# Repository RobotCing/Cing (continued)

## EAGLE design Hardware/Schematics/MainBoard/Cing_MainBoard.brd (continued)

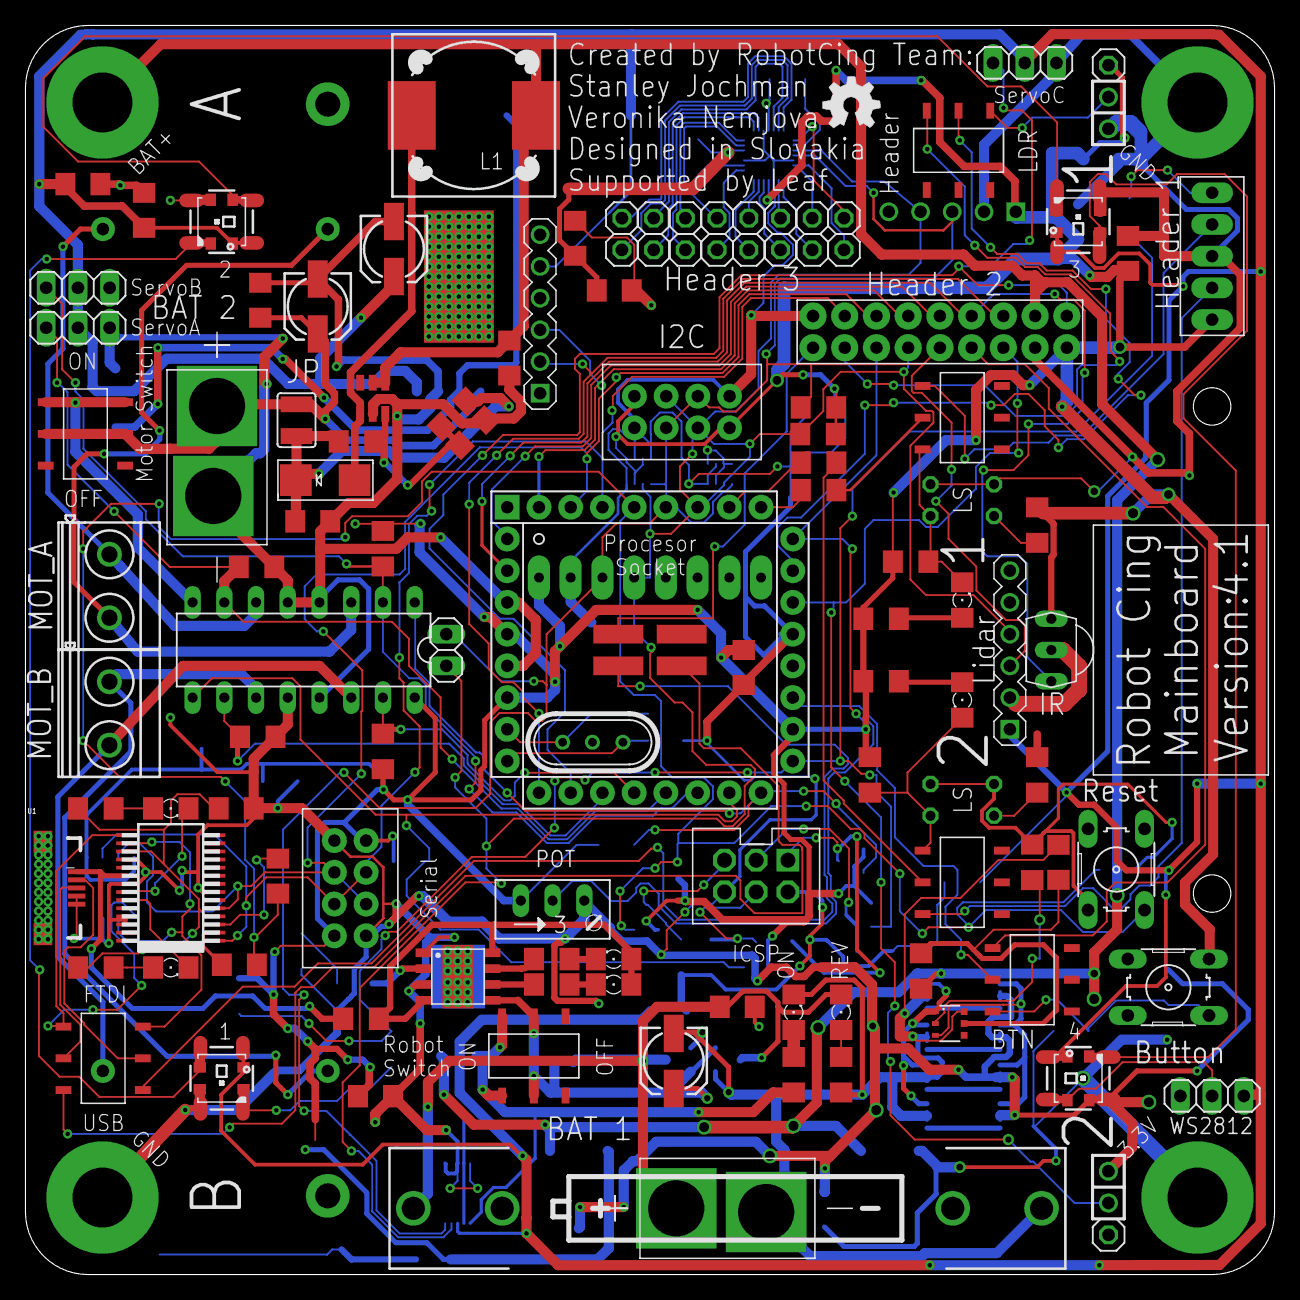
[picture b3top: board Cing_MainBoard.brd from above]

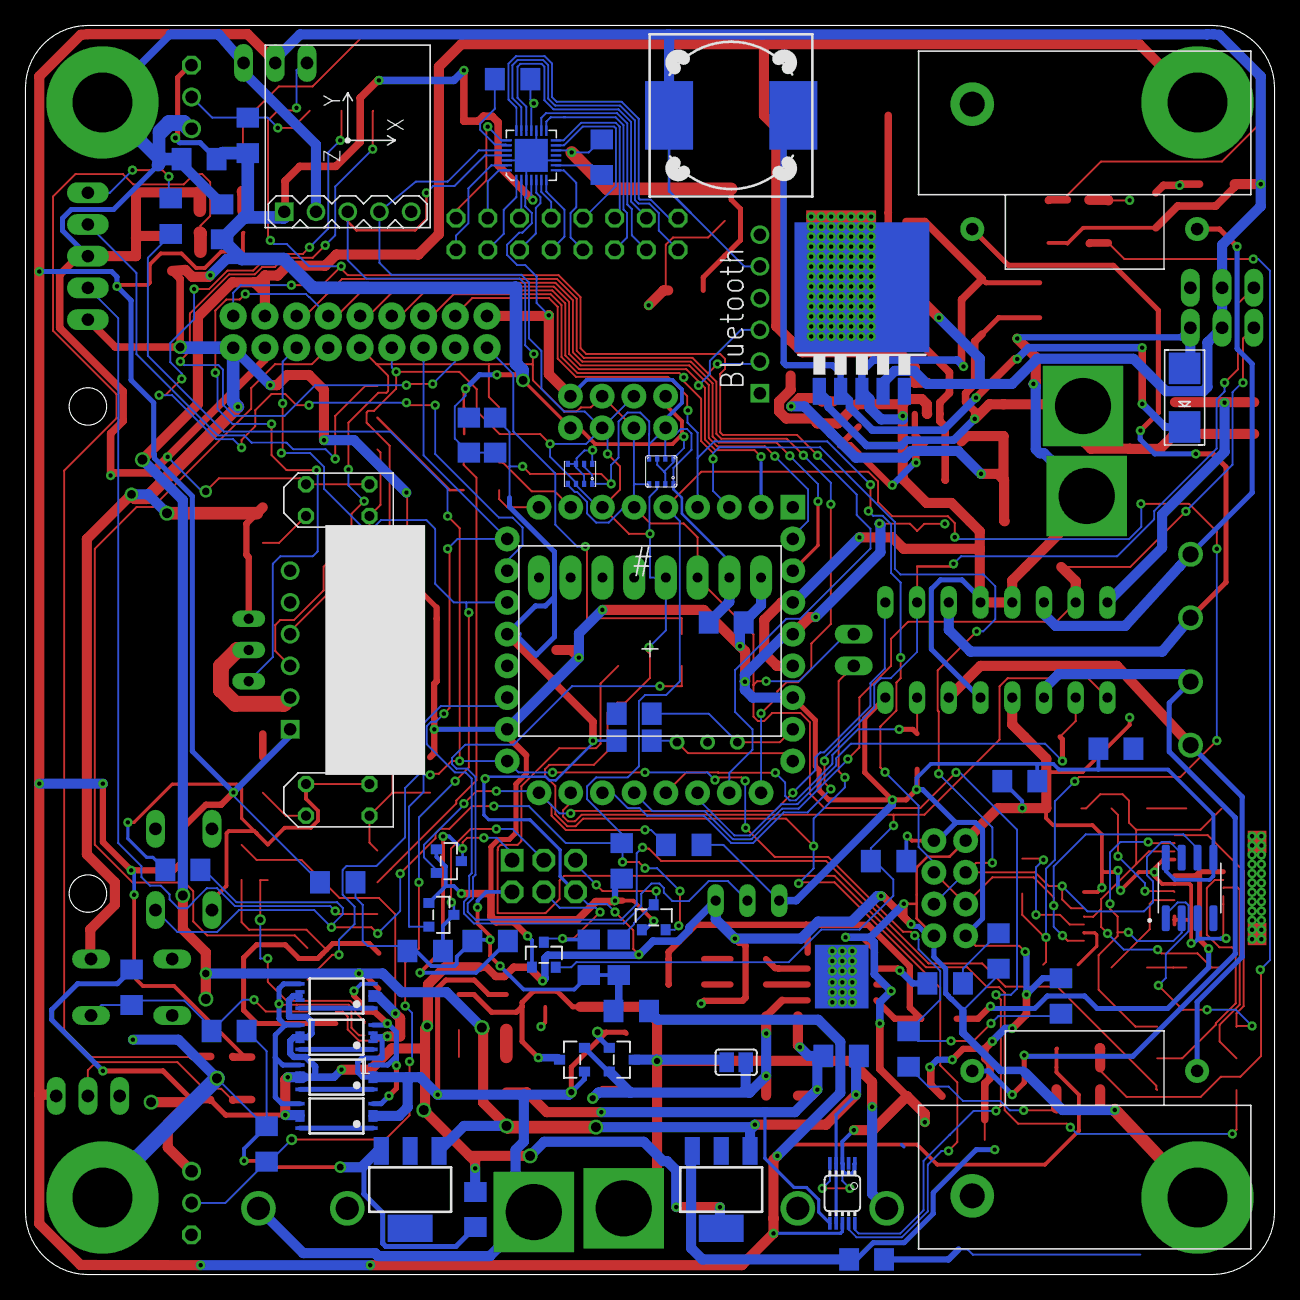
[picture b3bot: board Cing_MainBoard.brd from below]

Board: 2 copper layers, 100.0 x 100.0 mm, 186 parts (58 on the bottom side), 118 nets.

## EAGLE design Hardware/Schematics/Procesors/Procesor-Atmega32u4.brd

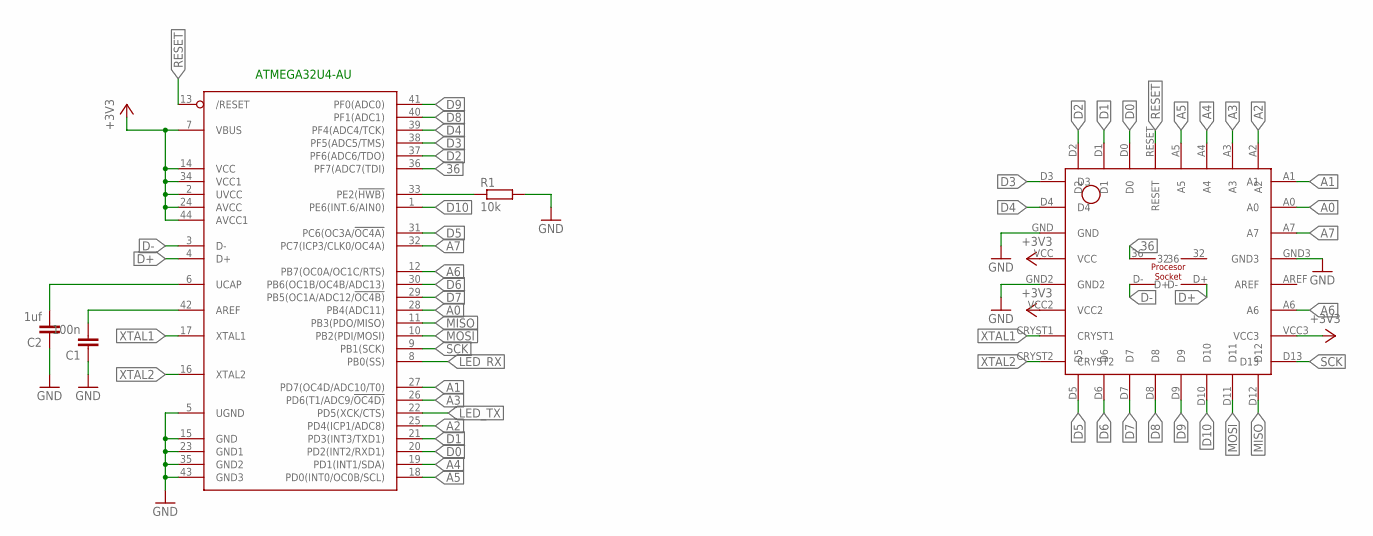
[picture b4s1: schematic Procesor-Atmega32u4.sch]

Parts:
ATMEGA32U4-AU: ATMEGA32U4-AU; TQFP44
C1: 100n; C1206
C2: 1uf; C1206K
R1: 10k; R1206
U$2: PROCESSOR-SOCKET; PROCESOR

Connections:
36: ATMEGA32U4-AU.36 (PF7(ADC7(TDI)), U$2.36
+3V3: ATMEGA32U4-AU.2 (UVCC), ATMEGA32U4-AU.7 (VBUS), ATMEGA32U4-AU.14 (VCC), ATMEGA32U4-AU.24 (AVCC), ATMEGA32U4-AU.34 (VCC1), ATMEGA32U4-AU.44 (AVCC1), U$2.VCC, U$2.VCC2, U$2.VCC3
A0: ATMEGA32U4-AU.28 (PB4(ADC11)), U$2.A0
A1: ATMEGA32U4-AU.27 (PD7(OC4D/ADC10/T0)), U$2.A1
A2: ATMEGA32U4-AU.25 (PD4(ICP1/ADC8)), U$2.A2
A3: ATMEGA32U4-AU.26 (PD6(T1/ADC9/!OC4D)), U$2.A3
A4: ATMEGA32U4-AU.19 (PD1(INT1/SDA)), U$2.A4
A5: ATMEGA32U4-AU.18 (PD0(INT0/OC0B/SCL)), U$2.A5
A6: ATMEGA32U4-AU.12 (PB7(OC0A/OC1C/RTS)), U$2.A6
A7: ATMEGA32U4-AU.32 (PC7(ICP3/CLK0/OC4A)), U$2.A7
D0: ATMEGA32U4-AU.20 (PD2(INT2/RXD1)), U$2.D0
D1: ATMEGA32U4-AU.21 (PD3(INT3/TXD1)), U$2.D1
D2: ATMEGA32U4-AU.37 (PF6(ADC6/TDO)), U$2.D2
D3: ATMEGA32U4-AU.38 (PF5(ADC5/TMS)), U$2.D3
D4: ATMEGA32U4-AU.39 (PF4(ADC4/TCK)), U$2.D4
D5: ATMEGA32U4-AU.31 (PC6(OC3A/!OC4A)), U$2.D5
D6: ATMEGA32U4-AU.30 (PB6(OC1B/OC4B/ADC13)), U$2.D6
D7: ATMEGA32U4-AU.29 (PB5(OC1A/ADC12/!OC4B)), U$2.D7
D8: ATMEGA32U4-AU.40 (PF1(ADC1)), U$2.D8
D9: ATMEGA32U4-AU.41 (PF0(ADC0)), U$2.D9
D10: ATMEGA32U4-AU.1 (PE6(INT.6/AIN0)), U$2.D10
D+: ATMEGA32U4-AU.4 (D+), U$2.D+
D-: ATMEGA32U4-AU.3 (D-), U$2.D-
GND: ATMEGA32U4-AU.5 (UGND), ATMEGA32U4-AU.15 (GND), ATMEGA32U4-AU.23 (GND1), ATMEGA32U4-AU.35 (GND2), ATMEGA32U4-AU.43 (GND3), C1.1, C2.1, R1.2, U$2.GND, U$2.GND2, U$2.GND3
LED_RX: ATMEGA32U4-AU.8 (PB0(SS))
LED_TX: ATMEGA32U4-AU.22 (PD5(XCK/CTS))
MISO: ATMEGA32U4-AU.11 (PB3(PDO/MISO)), U$2.D12
MOSI: ATMEGA32U4-AU.10 (PB2(PDI/MOSI)), U$2.D11
unnamed: ATMEGA32U4-AU.42 (AREF), C1.2
unnamed: ATMEGA32U4-AU.6 (UCAP), C2.2
unnamed: ATMEGA32U4-AU.33 (PE2(!HWB)), R1.1
RESET: ATMEGA32U4-AU.13 (/RESET), U$2.RESET
SCK: ATMEGA32U4-AU.9 (PB1(SCK)), U$2.D13
XTAL1: ATMEGA32U4-AU.17 (XTAL1), U$2.CRYST1
XTAL2: ATMEGA32U4-AU.16 (XTAL2), U$2.CRYST2

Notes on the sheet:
ATMEGA32U4-AU

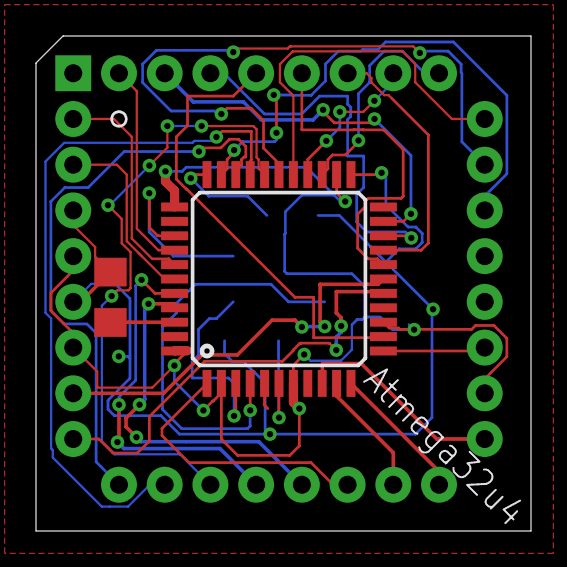
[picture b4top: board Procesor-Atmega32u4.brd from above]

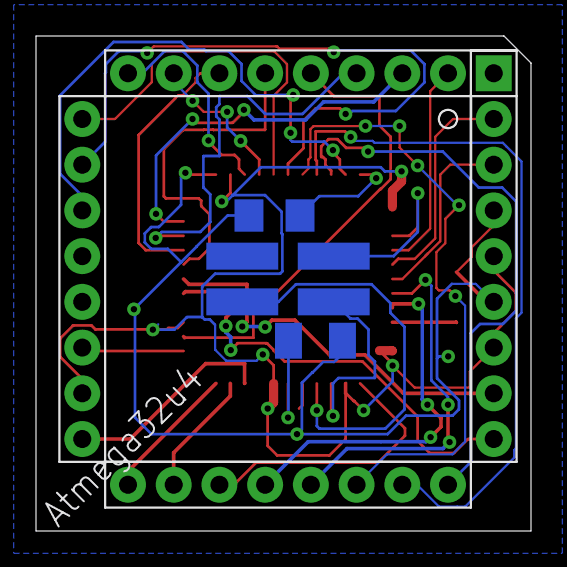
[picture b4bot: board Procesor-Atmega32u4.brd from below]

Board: 2 copper layers, 27.5 x 27.5 mm, 5 parts (2 on the bottom side), 33 nets.

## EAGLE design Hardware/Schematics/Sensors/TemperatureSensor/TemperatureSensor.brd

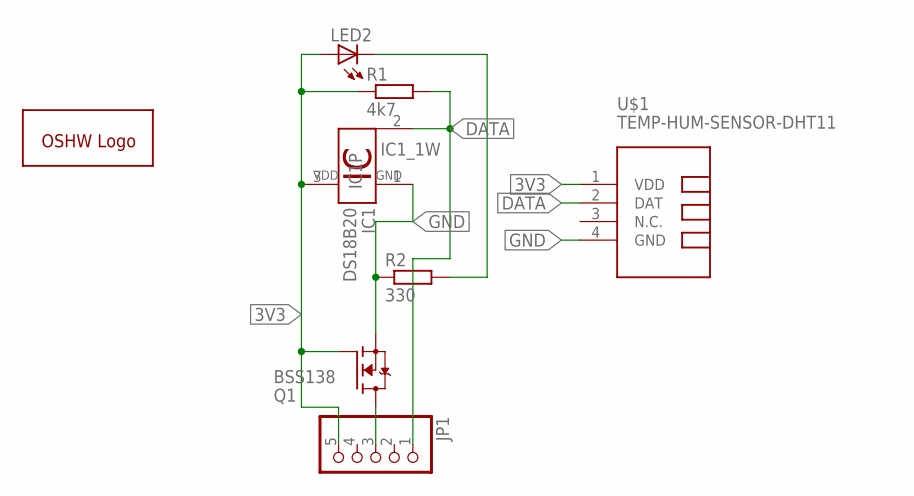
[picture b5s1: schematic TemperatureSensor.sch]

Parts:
IC1: DS18B20; TO92-
JP1: PINHD-1X5; 1X05
LED2: LEDSMT1206; 1206
Q1: BSS138; SOT23
R1: 4k7; R1206
R2: 330; R1206
U$1: TEMP-HUM-SENSOR-DHT11
U$2: OPENSOURCE; OSHW_5MM

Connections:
3V3: IC1.3 (VDD), JP1.5, LED2.A, Q1.1 (G), R1.1, U$1.1 (VDD)
DATA: IC1.2 (1W), JP1.1, R1.2, U$1.2 (DAT)
GND: IC1.1 (GND), Q1.2 (S), R2.1, U$1.4 (GND)
unnamed: LED2.C, R2.2
unnamed: JP1.3, Q1.3 (D)

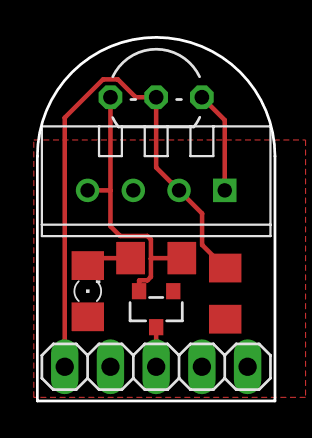
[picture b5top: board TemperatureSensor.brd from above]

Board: 2 copper layers, 13.2 x 20.2 mm, 8 parts (1 on the bottom side), 5 nets.

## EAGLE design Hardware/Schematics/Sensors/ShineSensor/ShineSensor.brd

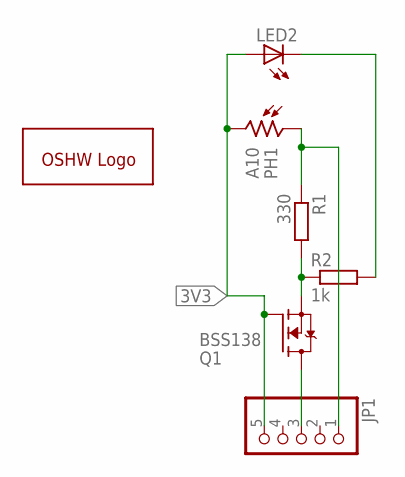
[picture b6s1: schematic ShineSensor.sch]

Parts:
JP1: PINHD-1X5; 1X05
LED2: LEDSMT1206; 1206
PH1: A10; T0-46-A10XX
Q1: BSS138; SOT23
R1: 330; R1206
R2: 1k; R1206
U$1: OPENSOURCE; OSHW_5MM

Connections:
3V3: JP1.5, LED2.A, PH1.2, Q1.1 (G)
unnamed: LED2.C, R2.2
unnamed: JP1.3, Q1.3 (D)
unnamed: JP1.1, PH1.1, R1.1
unnamed: Q1.2 (S), R1.2, R2.1

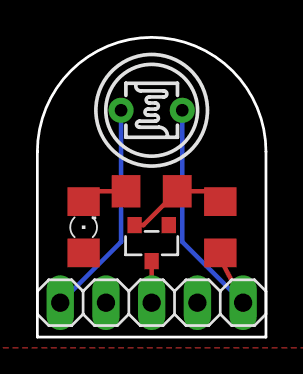
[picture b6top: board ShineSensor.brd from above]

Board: 2 copper layers, 12.7 x 16.7 mm, 7 parts (1 on the bottom side), 5 nets.

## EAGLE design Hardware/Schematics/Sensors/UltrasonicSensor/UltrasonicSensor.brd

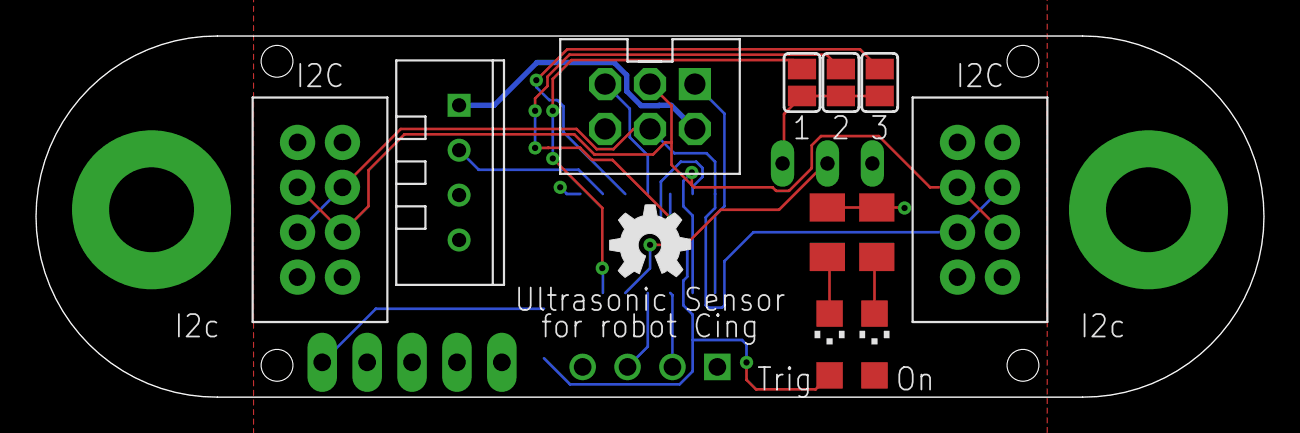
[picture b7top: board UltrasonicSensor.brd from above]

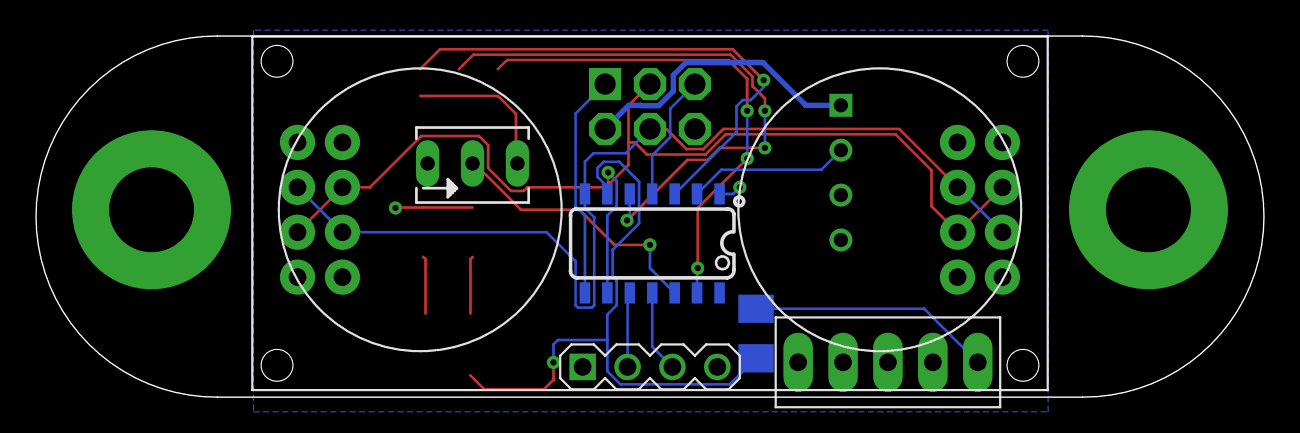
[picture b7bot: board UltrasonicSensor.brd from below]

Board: 2 copper layers, 69.5 x 20.4 mm, 19 parts (5 on the bottom side), 17 nets.

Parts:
JP1: ICSP_HEADER
LED1, LED3: CHIPLED_1206
R1, R3: 100R; M1206
R2: 100k; B64Y
R4: 1k; M1206
SJ1, SJ3, SJ5: SJ
U$1: ULTRASONIC-HC-SR04
U$2: ATTINY84; SO14
U$3, U$4: I2C_HEADER; I2_HEADER
U$5: OPENSOURCE; OSHW_5MM
U$6: CONNECTOR_1X5
U$7: TEMP-HUM-SENSOR-DHT11
U$8, U$9: LEGO-1X1

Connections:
0: SJ5.1, U$2.13
8: SJ3.1, U$2.5
9: SJ1.1, U$2.3
+3V3: JP1.2, LED1.A, R2.E, U$1.1, U$2.1, U$3.5V, U$3.+5V, U$4.5V, U$4.+5V, U$6.+5V, U$7.1
DAT: U$2.2, U$7.2
ECHO: U$1.3, U$2.11
GND: JP1.6, R1.2, R2.A, R3.1, SJ1.2, SJ3.2, SJ5.2, U$1.4, U$2.14, U$3.GND1, U$3.GND2, U$4.GND1, U$4.GND2, U$6.GND, U$7.4
MISO: JP1.1, U$2.8
unnamed: R4.2, U$6.A1
unnamed: LED1.C, R1.1
unnamed: LED3.C, R3.2
OUTPUT: LED3.A, R4.1, U$2.6
POT: R2.S, U$2.12
RESET: JP1.5, U$2.4
SCL: JP1.3, U$2.9, U$3.SCL, U$3.SCL2, U$4.SCL, U$4.SCL2
SDA: JP1.4, U$2.7, U$3.SDA, U$3.SDA2, U$4.SDA, U$4.SDA2
TRIG: U$1.2, U$2.10

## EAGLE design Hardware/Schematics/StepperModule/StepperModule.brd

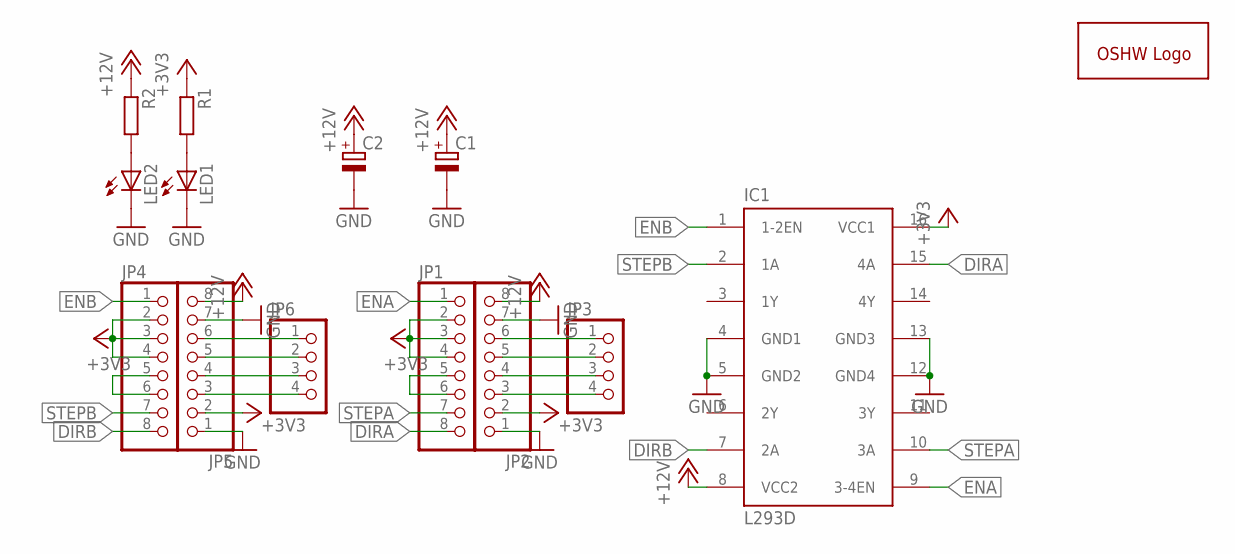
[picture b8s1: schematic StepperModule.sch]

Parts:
C1, C2: CPOL-EUTT5D9; TT5D9
IC1: L293D; L293
JP1, JP2, JP4, JP5: PINHD-1X8; 1X08
JP3, JP6: PINHD-1X4; 1X04
LED1, LED2: LEDSML1206; SML1206
R1, R2: R-EU_M1206; M1206
U$5: OPENSOURCE; OSHW_5MM

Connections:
+3V3: IC1.16 (VCC1), JP1.2, JP1.3, JP1.4, JP2.2, JP4.2, JP4.3, JP4.4, JP5.2, R1.1
+12V: C1.+, C2.+, IC1.8 (VCC2), JP2.8, JP5.8, R2.1
DIRA: IC1.15 (4A), JP1.8
DIRB: IC1.7 (2A), JP4.8
ENA: IC1.9 (3-4EN), JP1.1
ENB: IC1.1 (1-2EN), JP4.1
GND: C1.-, C2.-, IC1.4 (GND1), IC1.5 (GND2), IC1.12 (GND4), IC1.13 (GND3), JP2.1, JP2.7, JP5.1, JP5.7, LED1.C, LED2.C
unnamed: LED1.A, R1.2
unnamed: LED2.A, R2.2
unnamed: JP4.5, JP4.6
unnamed: JP1.5, JP1.6
unnamed: JP5.3, JP6.4
unnamed: JP5.4, JP6.3
unnamed: JP2.3, JP3.4
unnamed: JP2.4, JP3.3
unnamed: JP2.5, JP3.2
unnamed: JP2.6, JP3.1
unnamed: JP5.5, JP6.2
unnamed: JP5.6, JP6.1
STEPA: IC1.10 (3A), JP1.7
STEPB: IC1.2 (1A), JP4.7

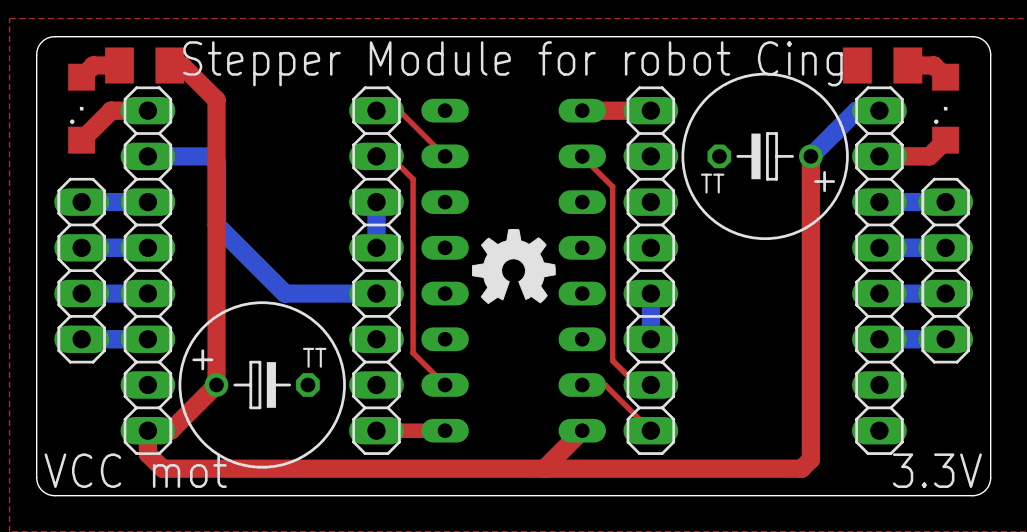
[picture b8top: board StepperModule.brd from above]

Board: 2 copper layers, 53.0 x 25.5 mm, 14 parts (1 on the bottom side), 21 nets.

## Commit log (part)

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2017-10-15 Kapitola: Bzučiak
2017-10-15 Rename 006_Tlačidlo.ino to 00_Tlačidlo.ino
2017-10-15 Kapitola: Tlačidlo
2017-10-15 Rename 005_Osvetlenie.ino to 00_Osvetlenie.ino
2017-10-15 Kapitola: Osvetlenie
2017-10-15 Rename 001_Chodenie rovno a dozadu.ino to 00_Chodenie rovno a dozadu.ino
2017-10-15 Kapitola: Pokračujeme v pohybe
2017-10-25 Create LICENSE
2017-11-08 Rename Programy/0007_Osvetlenie.ino to kniha/0007_Osvetlenie.ino
2017-11-08 Kapitola: Prekážky
2017-11-08 Rename _0002_Osvetlenie.ino to 0002_Osvetlenie.ino
2017-11-08 Rename _0003_Tlacidlo.ino to 0003_Tlačidlo.ino
2017-11-08 Kapitola: Nastavujeme hodnotu
2017-11-08 Kapitola: Svetelná signalizácia
2017-11-08 Kapitola: Meranie teploty
2018-06-04 ESP8266 Procesor Board
2018-07-14 Remove invalid reference link from keywords.txt
    The third field of keywords.txt is used to provide Arduino Language Reference links, which are accessed from the Arduino IDE by highlighting the keyword and then selecting "Find in Reference" from th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
    Reference:
    https://github.com/arduino/Arduino/wiki/Arduino-IDE-1.5:-Library-specification#keywordstxt-format
2018-07-18 Fix bad URLs in library.properties
2018-07-22 Arduino example
2018-07-31 Cing Libraries
    Adding .zip libraries
2018-08-05 Deleting Schematic Folder
2018-08-05 Removing Schemy folder
2018-08-05 Schematic files upload
2018-08-05 Adding pin 36
2018-08-06 Removing old examples
2018-08-07 Adding optional 3V3 regulator
2018-08-07 Organising folders
2018-08-07 Update to edit
2018-09-13 commiting files
2018-09-13 editing constructor
2018-10-20 Mainboard Upgrade
2018-10-29 upgrading board
2018-11-17 sensors
2018-11-18 Final
2018-11-28 board change
2018-11-30 Speak modul addon
2018-12-17 USBasp firmware
2018-12-20 Version 3.0
2018-12-28 .zip libraries
2019-01-02 Cing libraries in .zip
2019-01-02 library.properties update
2019-01-03 moving libraries to other repo
2019-01-12 Examples
2019-01-31 renaming file
2019-02-02 Example for counting lines
2019-02-02 Example for Setting variable value
2019-02-05 Program for goind forward and backward
2019-02-10 Board fixes
2019-02-21 Adding Sensor readout
2019-03-09 Ultrasonic sensor
2019-03-10 Adding better P-fet
2019-04-10 Patches
2019-04-10 Adding UltrasonicSensor software
2019-04-11 BoardManager 3.0.0
2019-04-11 Package update
2019-04-12 Board Manager 3.0.0
2019-05-04 gerber update
2019-05-22 3.0.1 support
2019-05-22 3.0.1 update
2019-06-15 PCB version 3.0.1
2019-06-15 Board version 3.1
2019-06-25 3D package upgrade
2019-06-29 Encoder motor controller
2019-06-29 board manager 4.0.0
2019-07-12 Panel
    contains procesors sensors and stepper driver
2019-07-18 adding more protection (motor fix)
2019-07-24 adding CH330N
2019-08-03 adding eagle files
2019-08-03 Windows install file
2019-08-03 Readme update for Windows and Linux
2019-08-03 updating serial port grab
2019-08-03 config file for Cing Checker
2019-08-03 adding setting support
2019-08-05 Rename LICENSE to LICENSE.md
2019-08-10 adding minor fixes
2019-08-10 minor changes
2019-08-11 4.1 board
2019-08-11 fixing some bugs
2019-08-14 panel for stepper motor procesors ultrasonic and sensors
2019-09-22 modifications
2019-09-28 small updates on Cing 4.1
2020-01-18 adding microbit package
2020-01-18 adding library exeption
2020-01-18 microbit procesor
2020-01-22 microBit board
2021-02-01 adding RPI_pico
